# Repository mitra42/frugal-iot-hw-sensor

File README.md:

# Frugal-IoT V0.2

A simple, un-opinionated, multi-purpose sensor board, that can be wired to sensors using most common interfaces (I2C, ModBus, OneWire, Analog) with onboard charging and external antenna.

**Status:** revision 4 (28 Oct 2026): 64 × 37 mm, 2 layers, routed, DRC clean; J4 (cell) and J6 (5 V in) now fitted (D34); JLCPCB files ready for the first order.

## Hardware Features

* ESP32-C3-WROOM-02U
* U.FL socket for external antenna. 
* USB-C for power and programming (e.g. using a $10 security camera solar panel)
* Protected charger circuitry for a single LiPo cell (~250mA), will work with really small cells (e.g. salvaged from vapes) or by adding a solder bridge can charge an 18650 cell at ~500mA
* Sensors controlled by a switched 3.3V sensor rail, allowing much lower power consumption in sleep.
* I2C support on J1 
* Two sensor inputs on J12 can be used for analog, OneWire etc, pads to add pull up resistor or smoothing capacitor if required.
* Two extra sensors on J13 (not soldered by default) 
* RS485(Modbus) on J3, (can be omitted to save ~USD1.00, or to get three more pins for sensors.
* 37mm * 64mm board with connectors mostly at the ends, so that it can fit inside a 40mm pipe as an affordable enclosure. 

## Software features

The board can be flashed with any software, but its designed to work well with [Frugal-IoT](https://github.com/mitra42/frugal-iot) which has the following features. 

* Support for a very wide and expanding range of sensors 
* Integrates with Frugal-IoT cloud, and UX on phone or laptop
* Plug and play MQTT interface, treats remote sensors and actuators the same as local ones 
* Captive WiFi portal for local configuration
* Local controls for on-device automation configured through the UX.
* Multilingual support on both captive portal and UX
* Automatic Over-The-Air (OTA) updates for unattended devices.
* Power management for really long life for sensors that report at long intervals.
* mDNS, for device to device signalling when the Internet is down
* NTP integration for accurate clock
* Fully Open-Source (i.e. not crippleware) 

## Files

| | |
|---|---|
| `SCHEMATIC.pdf` | schematic, one sheet |
| `BOM.csv` | bill of materials with LCSC (JLCPCB) part numbers; DNP = not fitted |
| `COST-ESTIMATE.txt` | JLCPCB cost for 10 and 100 boards, and the saving without Modbus |
| `PCB-LAYOUT.pdf` | 3D views and both copper layers |
| `DECISIONS.md` | design decisions and why |
| `fabrication/` | files to order from JLCPCB — see its README |
| `frugal_iot_v02/` | KiCad 10 project |
| `firmware/` | PlatformIO env for frugal-iot-demo + board variant (pins_arduino.h) |
| `claude-tools/` | scripts Claude uses to regenerate the design — reviewers can ignore |

The schematic is generated from `claude-tools/schematic/circuit.py`: changes made by Claude go there, not into
the .kicad_sch. Regenerate: `buildlib.py`, `run_draw_bg.sh` (log must end `VERIFY OK`), `run_kicad.sh`,
then `jlc_dump.sh` and `python3 cost_estimate.py > ../../COST-ESTIMATE.txt` (see ../irrigation-layout-oct-2026/claude-tools/README.md for the method).

If the fabrication and KiCad directories are not available wherever you find this, please let me know (mitra@mitra.biz) and I'll send you them.

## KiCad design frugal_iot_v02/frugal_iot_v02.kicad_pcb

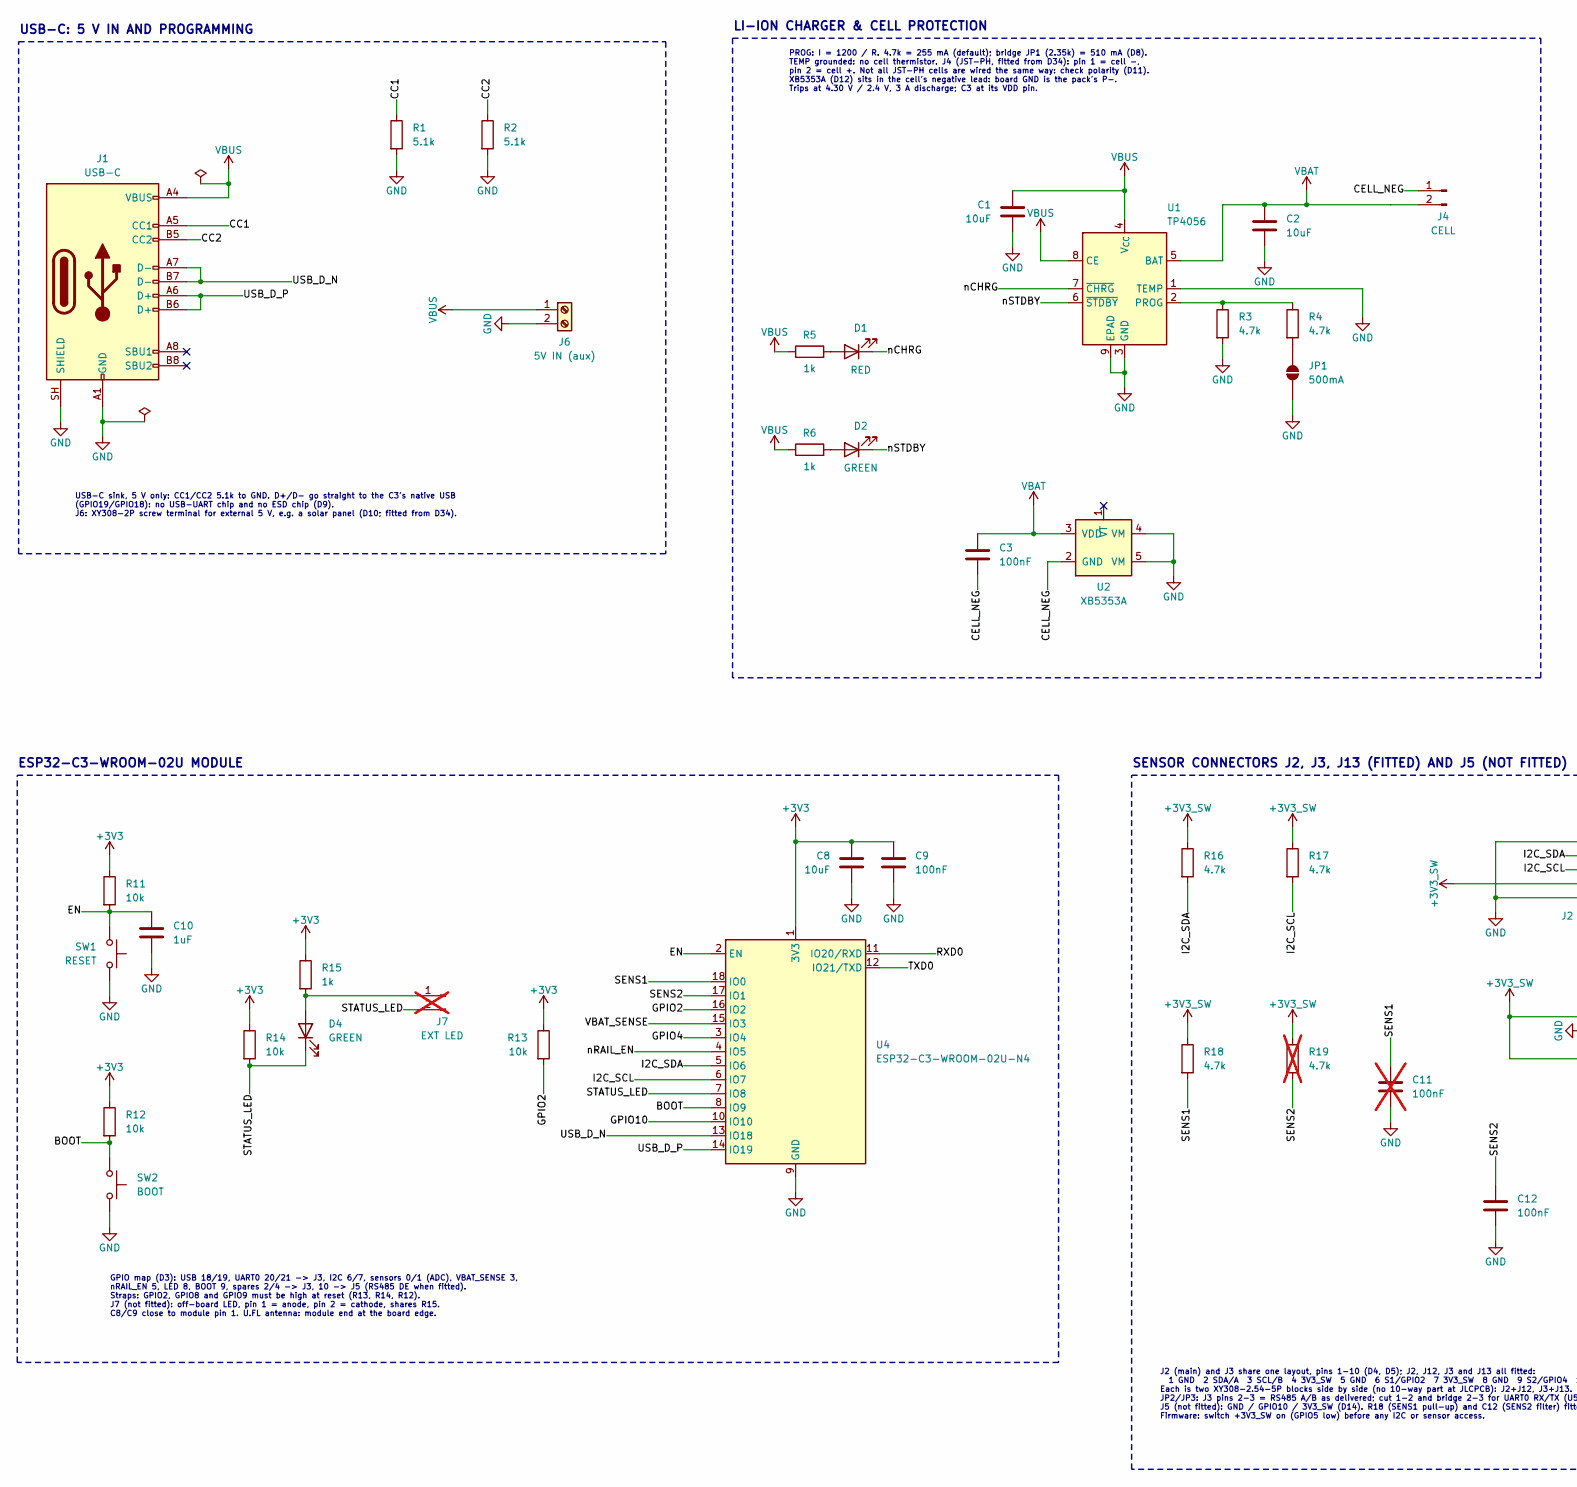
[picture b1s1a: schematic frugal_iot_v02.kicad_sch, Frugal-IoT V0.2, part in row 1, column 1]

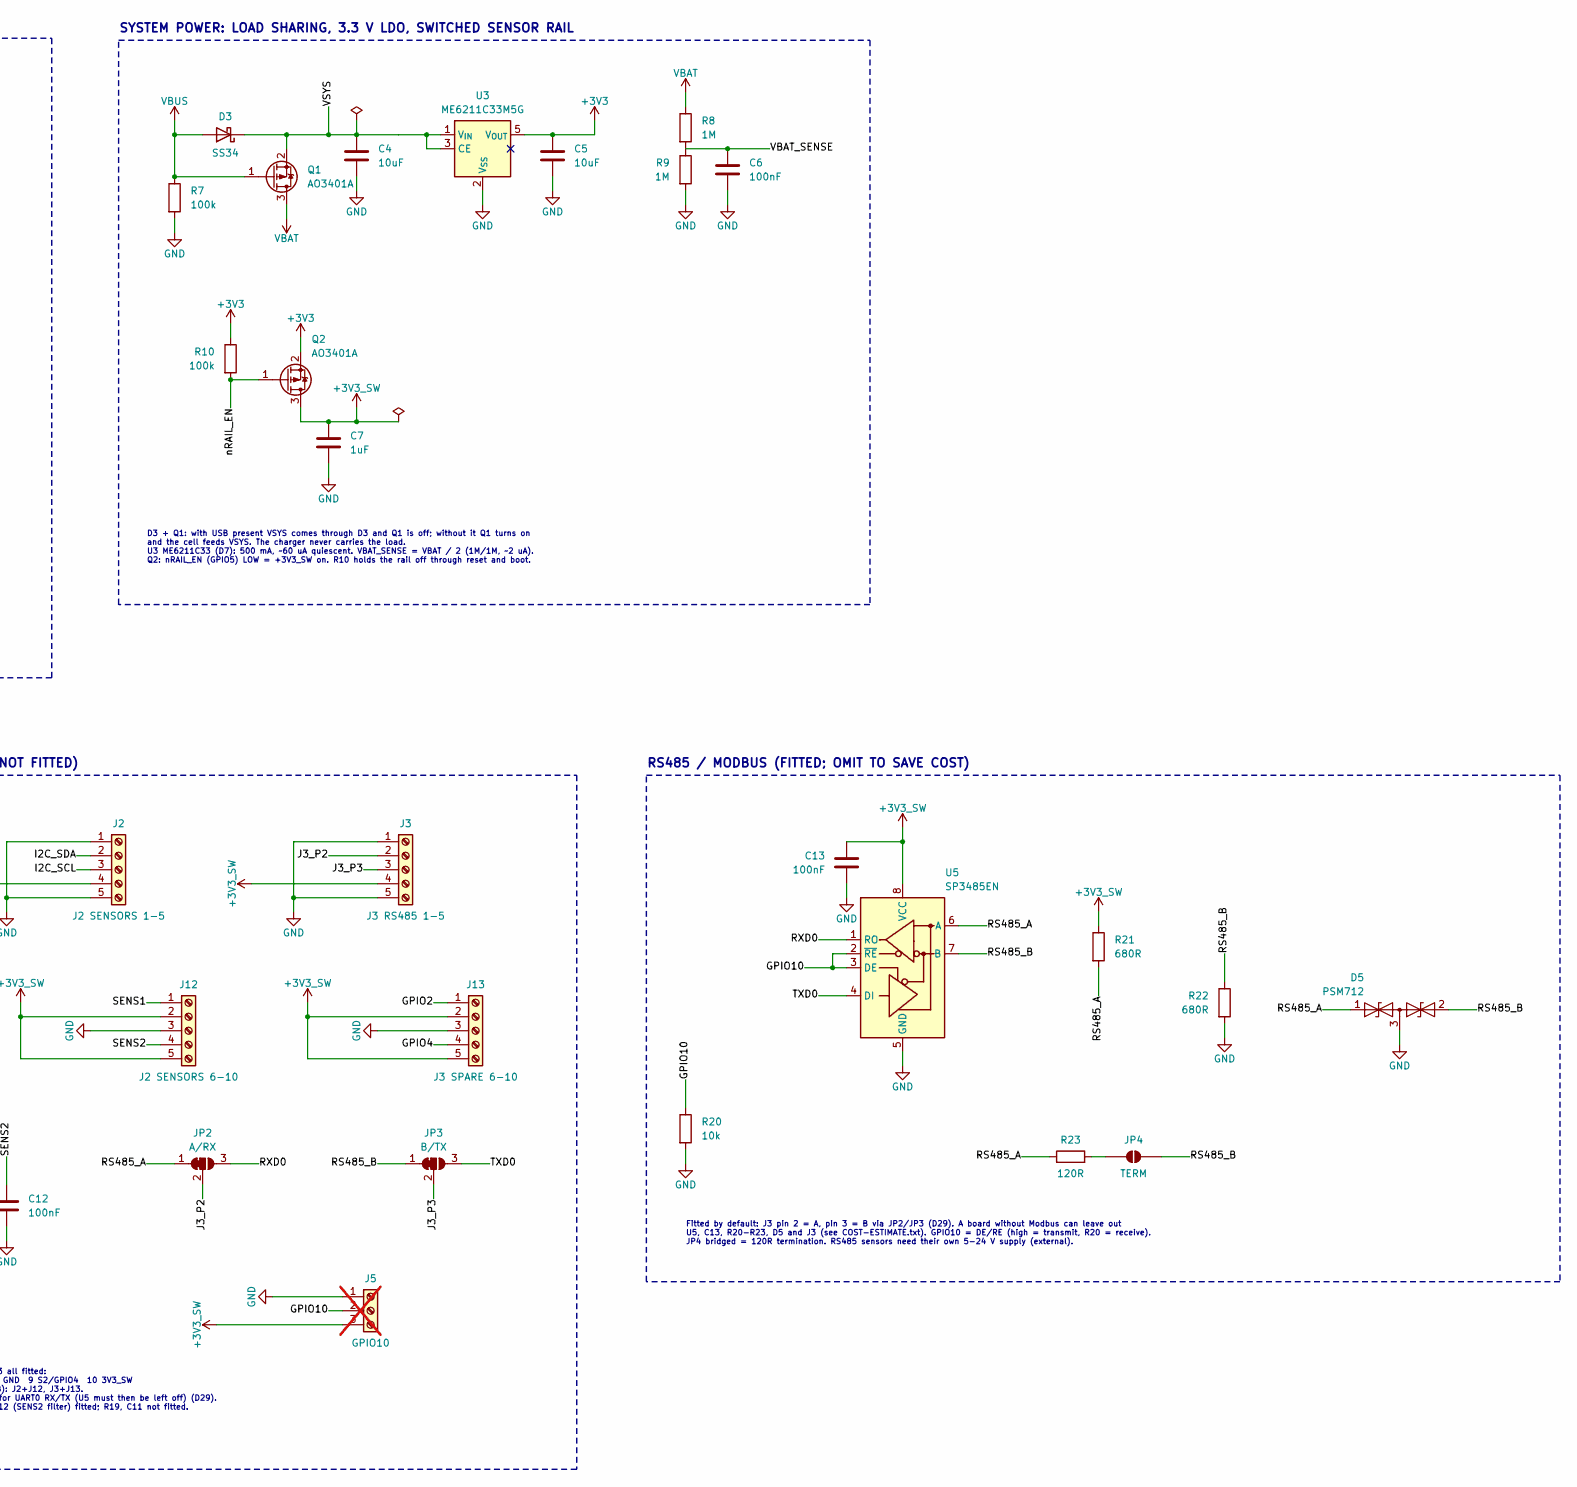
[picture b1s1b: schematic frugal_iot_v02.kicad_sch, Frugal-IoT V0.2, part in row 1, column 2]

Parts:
C1, C2, C4, C5, C8: 10uF; C_0603_1608Metric; MPN 10uF; LCSC C19702
C3, C6, C9, C12, C13: 100nF; C_0603_1608Metric; MPN 100nF; LCSC C14663
C7, C10: 1uF; C_0603_1608Metric; MPN 1uF; LCSC C15849
C11: 100nF; C_0603_1608Metric; MPN 100nF; LCSC C14663; not fitted
D1: RED; LED_0603_1608Metric; MPN KT-0603R; LCSC C2286
D2, D4: GREEN; LED_0805_2012Metric; MPN KT-0805G; LCSC C2297
D3: SS34; D_SMA; MPN SS34; LCSC C8678
D5: PSM712; SOT-23; MPN PSM712-LF-T7; LCSC C32677
J1: USB-C; USB_C_Receptacle_HRO_TYPE-C-31-M-12; MPN TYPE-C-31-M-12; LCSC C165948
J2: J2 SENSORS 1-5; TerminalBlock_Xinya_XY308-2.54-5P_1x05_P2.54mm_Horizontal; MPN XY308-2.54-5P; LCSC C915914
J3: J3 RS485 1-5; TerminalBlock_Xinya_XY308-2.54-5P_1x05_P2.54mm_Horizontal; MPN XY308-2.54-5P; LCSC C915914
J4: CELL; JST_PH_S2B-PH-K_1x02_P2.00mm_Horizontal; MPN S2B-PH-K-S; LCSC C173752
J5: GPIO10; TerminalBlock_Xinya_XY308-2.54-3P_1x03_P2.54mm_Horizontal; MPN XY308-2.54-3P; LCSC C557686; not fitted
J6: 5V IN (aux); TerminalBlock_Xinya_XY308-2.54-2P_1x02_P2.54mm_Horizontal; MPN XY308-2.54-2P; LCSC C557685
J7: EXT LED; PinHeader_1x02_P2.54mm_Vertical; MPN EXT LED; not fitted
J12: J2 SENSORS 6-10; TerminalBlock_Xinya_XY308-2.54-5P_1x05_P2.54mm_Horizontal; MPN XY308-2.54-5P; LCSC C915914
J13: J3 SPARE 6-10; TerminalBlock_Xinya_XY308-2.54-5P_1x05_P2.54mm_Horizontal; MPN XY308-2.54-5P; LCSC C915914
JP1: 500mA; SolderJumper-2_P1.3mm_Open_RoundedPad1.0x1.5mm; MPN 500mA
JP2: A/RX; SolderJumper-3_P1.3mm_Bridged12_RoundedPad1.0x1.5mm; MPN A/RX
JP3: B/TX; SolderJumper-3_P1.3mm_Bridged12_RoundedPad1.0x1.5mm; MPN B/TX
JP4: TERM; SolderJumper-2_P1.3mm_Open_RoundedPad1.0x1.5mm; MPN TERM
Q1, Q2: AO3401A; SOT-23; MPN AO3401A; LCSC C15127
R1, R2: 5.1k; R_0603_1608Metric; MPN 5.1k; LCSC C23186
R3, R4, R16, R17, R18: 4.7k; R_0603_1608Metric; MPN 4.7k; LCSC C23162
R5, R6, R15: 1k; R_0603_1608Metric; MPN 1k; LCSC C21190
R7, R10: 100k; R_0603_1608Metric; MPN 100k; LCSC C25803
R8, R9: 1M; R_0603_1608Metric; MPN 1M; LCSC C22935
R11, R12, R13, R14, R20: 10k; R_0603_1608Metric; MPN 10k; LCSC C25804
R19: 4.7k; R_0603_1608Metric; MPN 4.7k; LCSC C23162; not fitted
R21, R22: 680R; R_0603_1608Metric; MPN 680R; LCSC C23228
R23: 120R; R_0603_1608Metric; MPN 120R; LCSC C22787
SW1: RESET; SW_Push_1P1T_XKB_TS-1187A; MPN TS-1187A-B-A-B; LCSC C318884
SW2: BOOT; SW_Push_1P1T_XKB_TS-1187A; MPN TS-1187A-B-A-B; LCSC C318884
U1: TP4056; SOIC-8-1EP_3.9x4.9mm_P1.27mm_EP2.41x3.3mm; MPN TP4056; LCSC C16581
U2: XB5353A; SOT-23-5; MPN XB5353A; LCSC C80628
U3: ME6211C33M5G; SOT-23-5; MPN ME6211C33M5G-N; LCSC C82942
U4: ESP32-C3-WROOM-02U-N4; ESP32-C3-WROOM-02U; MPN ESP32-C3-WROOM-02U-N4; LCSC C2926676
U5: SP3485EN; SOIC-8_3.9x4.9mm_P1.27mm; MPN SP3485EN-L/TR; LCSC C8963

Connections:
+3V3: C5.1, C8.1, C9.1, Q2.2 (S), R10.1, R11.1, R12.1, R13.1, R14.1, R15.1, U3.5 (V_{OUT}), U4.1 (3V3)
/BOOT: R12.2, SW2.1, U4.8 (IO9)
/CC1: J1.A5 (CC1), R1.1
/CC2: J1.B5 (CC2), R2.1
/CELL_NEG: C3.2, J4.1, U2.2 (GND)
/EN: C10.1, R11.2, SW1.1, U4.2 (EN)
/GPIO2: J13.1, R13.2, U4.16 (IO2)
/GPIO4: J13.4, U4.3 (IO4)
/GPIO10: J5.2, R20.1, U4.10 (IO10), U5.2 (~RE), U5.3 (DE)
/I2C_SCL: J2.3, R17.2, U4.6 (IO7)
/I2C_SDA: J2.2, R16.2, U4.5 (IO6)
/J3_P2: J3.2, JP2.2 (C)
/J3_P3: J3.3, JP3.2 (C)
/RS485_A: D5.1 (A1), JP2.1 (A), R21.2, R23.1, U5.6 (A)
/RS485_B: D5.2 (A2), JP3.1 (A), JP4.2 (B), R22.1, U5.7 (B)
/RXD0: JP2.3 (B), U4.11 (IO20/RXD), U5.1 (RO)
/SENS1: C11.1, J12.1, R18.2, U4.18 (IO0)
/SENS2: C12.1, J12.4, R19.2, U4.17 (IO1)
/STATUS_LED: D4.1 (K), J7.2, R14.2, U4.7 (IO8)
/TXD0: JP3.3 (B), U4.12 (IO21/TXD), U5.4 (DI)
/USB_D_N: J1.A7 (D-), J1.B7 (D-), U4.13 (IO18)
/USB_D_P: J1.A6 (D+), J1.B6 (D+), U4.14 (IO19)
/VBAT_SENSE: C6.1, R8.2, R9.1, U4.15 (IO3)
/nCHRG: D1.1 (K), U1.7 (~CHRG)
/nRAIL_EN: Q2.1 (G), R10.2, U4.4 (IO5)
/nSTDBY: D2.1 (K), U1.6 (~STDBY)
unnamed: D1.2 (A), R5.2
unnamed: D2.2 (A), R6.2
unnamed: D4.2 (A), J7.1, R15.2
unnamed: JP1.1 (A), R4.2
unnamed: JP4.1 (A), R23.2
unnamed: R3.1, R4.1, U1.2 (PROG)
VBAT: C2.1, C3.1, J4.2, Q1.3 (D), R8.1, U1.5 (BAT), U2.3 (VDD)

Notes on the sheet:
D3 + Q1: with USB present VSYS comes through D3 and Q1 is off; without it Q1 turns on and the cell feeds VSYS. The charger never carries the load. U3 ME6211C33 (D7): 500 mA, ~60 uA quiescent. VBAT_SENSE = VBAT / 2 (1M/1M, ~2 uA). Q2: nRAIL_EN (GPIO5) LOW = +3V3_SW on. R10 holds the rail off through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
ESP32-C3-WROOM-02U MODULE
RS485 / MODBUS (FITTED; OMIT TO SAVE COST)
J2 (main) and J3 share one layout, pins 1-10 (D4, D5); J2, J12, J3 and J13 all fitted: 1 GND 2 SDA/A 3 SCL/B 4 3V3_SW 5 GND 6 S1/GPIO2 7 3V3_SW 8 GND 9 S2/GPIO4 10 3V3_SW Each is two XY308-2.54-5P blocks side by side (no 10-way part at JLCPCB): J2+J12, J3+J13. JP2/JP3: J3 pins 2-3 = RS485 A/B as de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
GPIO map (D3): USB 18/19, UART0 20/21 -> J3, I2C 6/7, sensors 0/1 (ADC), VBAT_SENSE 3, nRAIL_EN 5, LED 8, BOOT 9, spares 2/4 -> J3, 10 -> J5 (RS485 DE when fitted). Straps: GPIO2, GPIO8 and GPIO9 must be high at reset (R13, R14, R12). J7 (not fitted): off-board LED, pin 1 = anode, pin 2 = cathode, 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
LI-ION CHARGER & CELL PROTECTION
USB-C sink, 5 V only: CC1/CC2 5.1k to GND. D+/D- go straight to the C3's native USB (GPIO19/GPIO18): no USB-UART chip and no ESD chip (D9). J6: XY308-2P screw terminal for external 5 V, e.g. a solar panel (D10; fitted from D34).
SYSTEM POWER: LOAD SHARING, 3.3 V LDO, SWITCHED SENSOR RAIL
PROG: I = 1200 / R. 4.7k = 255 mA (default); bridge JP1 (2.35k) = 510 mA (D8). TEMP grounded: no cell thermistor. J4 (JST-PH, fitted from D34): pin 1 = cell -, pin 2 = cell +. Not all JST-PH cells are wired the same way: check polarity (D11). XB5353A (D12) sits in the cell's negative lead: board GN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
USB-C: 5 V IN AND PROGRAMMING
Fitted by default: J3 pin 2 = A, pin 3 = B via JP2/JP3 (D29). A board without Modbus can leave out U5, C13, R20-R23, D5 and J3 (see COST-ESTIMATE.txt). GPIO10 = DE/RE (high = transmit, R20 = receive). JP4 bridged = 120R termination. RS485 sensors need their own 5-24 V supply (external).
SENSOR CONNECTORS J2, J3, J13 (FITTED) AND J5 (NOT FITTED)

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
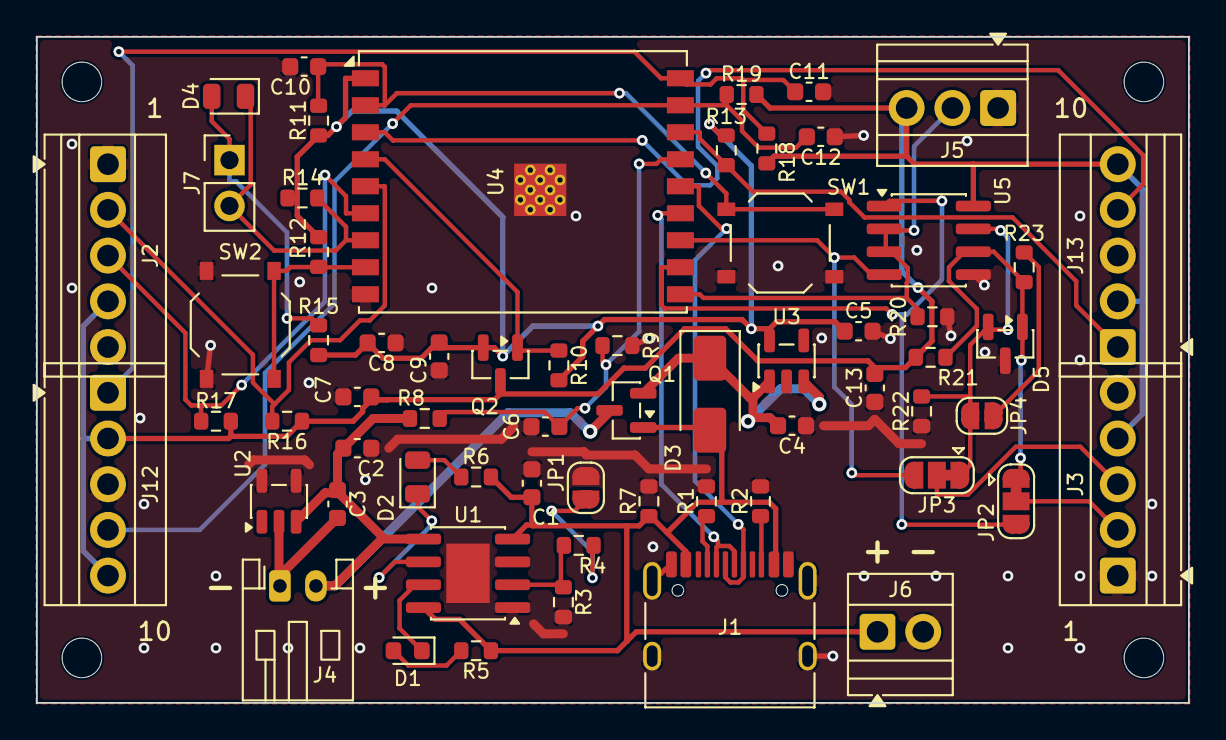
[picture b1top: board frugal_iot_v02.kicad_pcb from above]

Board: 2 copper layers, 64.0 x 37.0 mm, 67 parts (0 on the bottom side), 37 nets.

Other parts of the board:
H1, H2, H3, H4: M2; MountingHole_2.2mm_M2

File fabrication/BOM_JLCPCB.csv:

Comment,Designator,Footprint,LCSC Part #
10uF,"C1,C2,C4,C5,C8",C_0603_1608Metric,C19702
100nF,"C3,C6,C9,C12,C13",C_0603_1608Metric,C14663
1uF,"C7,C10",C_0603_1608Metric,C15849
RED,D1,LED_0603_1608Metric,C2286
GREEN,"D2,D4",LED_0805_2012Metric,C2297
SS34,D3,D_SMA,C8678
PSM712,D5,SOT-23,C32677
USB-C,J1,USB_C_Receptacle_HRO_TYPE-C-31-M-12,C165948
J2 SENSORS 1-5,"J2,J3,J12,J13",TerminalBlock_Xinya_XY308-2.54-5P_1x05_P2.54mm_Horizontal,C915914
CELL,J4,JST_PH_S2B-PH-K_1x02_P2.00mm_Horizontal,C173752
5V IN (aux),J6,TerminalBlock_Xinya_XY308-2.54-2P_1x02_P2.54mm_Horizontal,C557685
AO3401A,"Q1,Q2",SOT-23,C15127
5.1k,"R1,R2",R_0603_1608Metric,C23186
4.7k,"R3,R4,R16,R17,R18",R_0603_1608Metric,C23162
1k,"R5,R6,R15",R_0603_1608Metric,C21190
100k,"R7,R10",R_0603_1608Metric,C25803
1M,"R8,R9",R_0603_1608Metric,C22935
10k,"R11,R12,R13,R14,R20",R_0603_1608Metric,C25804
680R,"R21,R22",R_0603_1608Metric,C23228
120R,R23,R_0603_1608Metric,C22787
RESET,"SW1,SW2",SW_Push_1P1T_XKB_TS-1187A,C318884
TP4056,U1,SOIC-8-1EP_3.9x4.9mm_P1.27mm_EP2.41x3.3mm,C16581
XB5353A,U2,SOT-23-5,C80628
ME6211C33M5G,U3,SOT-23-5,C82942
ESP32-C3-WROOM-02U-N4,U4,ESP32-C3-WROOM-02U,C2926676
SP3485EN,U5,SOIC-8_3.9x4.9mm_P1.27mm,C8963

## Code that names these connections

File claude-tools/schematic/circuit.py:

"""Circuit definition for Frugal-IoT V0.2 (source of truth for parts and nets).
Each part: dict(prefix, lib, value, fp, nets{pin:net}, dnp, lcsc, mpn, block, note, ref)
net 'NC' => no-connect marker. Decisions referenced as Dn are in ../../DECISIONS.md.
"""
P = []
def part(prefix, lib, value, fp, nets, block, dnp=False, lcsc='', mpn='', rot=None, note='', ref=None):
    P.append(dict(prefix=prefix, lib=lib, value=value, fp=fp, nets=nets, block=block,
                  dnp=dnp, lcsc=lcsc, mpn=mpn, rot=rot, note=note, ref=ref))

R06 = 'Resistor_SMD:R_0603_1608Metric'; C06 = 'Capacitor_SMD:C_0603_1608Metric'
LED06 = 'LED_SMD:LED_0603_1608Metric'; LED08 = 'LED_SMD:LED_0805_2012Metric'
SMA = 'Diode_SMD:D_SMA'; SOT23 = 'Package_TO_SOT_SMD:SOT-23'
TB254 = 'TerminalBlock:TerminalBlock_Xinya_XY308-2.54-{n}P_1x0{n}_P2.54mm_Horizontal'
HDR = 'Connector_PinHeader_2.54mm:PinHeader_1x0{n}_P2.54mm_Vertical'
BTN = 'Button_Switch_SMD:SW_Push_1P1T_XKB_TS-1187A'
SJ = 'Jumper:SolderJumper-2_P1.3mm_Open_RoundedPad1.0x1.5mm'
SJ3 = 'Jumper:SolderJumper-3_P1.3mm_Bridged12_RoundedPad1.0x1.5mm'
XY = {2: ('C557685', 'XY308-2.54-2P'), 3: ('C557686', 'XY308-2.54-3P'), 5: ('C915914', 'XY308-2.54-5P')}

RES = {'10k': 'C25804', '100k': 'C25803', '1k': 'C21190', '4.7k': 'C23162', '5.1k': 'C23186',
       '1M': 'C22935', '120R': 'C22787', '680R': 'C23228'}
CAP = {'100nF': 'C14663', '1uF': 'C15849', '10uF': 'C19702'}

def R(v, a, b, blk, dnp=False, note=''):
    part('R', 'Device:R', v, R06, {'1': a, '2': b}, blk, dnp, RES.get(v, ''), note=note)
def C(v, a, b, blk, dnp=False, note=''):
    part('C', 'Device:C', v, C06, {'1': a, '2': b}, blk, dnp, CAP.get(v, ''), note=note)
def LED(col, anode, cathode, blk):  # JLCPCB Basic: red KT-0603R, green KT-0805G
    part('D', 'Device:LED', col, {'RED': LED06, 'GREEN': LED08}[col], {'2': anode, '1': cathode}, blk, rot=180,
         lcsc={'RED': 'C2286', 'GREEN': 'C2297'}[col], mpn={'RED': 'KT-0603R', 'GREEN': 'KT-0805G'}[col])
def PFET(g, s, d, blk):
    part('Q', 'Transistor_FET:AO3401A', 'AO3401A', SOT23, {'1': g, '2': s, '3': d}, blk, lcsc='C15127')
def BUTTON(a, b, blk, val):
    part('SW', 'Switch:SW_Push', val, BTN, {'1': a, '2': b}, blk, lcsc='C318884', mpn='TS-1187A-B-A-B')
def TERM(ref, n, nets, blk, val, dnp=False):
    lc, mpn = XY[n]
    part('J', f'Connector:Screw_Terminal_01x0{n}', val, TB254.format(n=n),
         {str(i + 1): net for i, net in enumerate(nets)}, blk, dnp, lc, mpn, ref=ref)

# ---------------- USB-C (power + native USB) ----------------
B = 'usb'
part('J', 'Connector:USB_C_Receptacle_USB2.0_16P', 'USB-C', 'Connector_USB:USB_C_Receptacle_HRO_TYPE-C-31-M-12',
     {'A1': 'GND', 'B1': 'GND', 'A12': 'GND', 'B12': 'GND', 'A4': 'VBUS', 'A9': 'VBUS', 'B4': 'VBUS', 'B9': 'VBUS',
      'A5': 'CC1', 'B5': 'CC2', 'A6': 'USB_D_P', 'B6': 'USB_D_P', 'A7': 'USB_D_N', 'B7': 'USB_D_N',
      'A8': 'NC', 'B8': 'NC', 'SH': 'GND'}, B, lcsc='C165948', mpn='TYPE-C-31-M-12', ref='J1')
R('5.1k', 'CC1', 'GND', B); R('5.1k', 'CC2', 'GND', B)
TERM('J6', 2, ['VBUS', 'GND'], B, '5V IN (aux)')   # D10: external 5 V beside USB; fitted from D34

# ---------------- Charger + cell protection ----------------
B = 'chg'
part('U', 'Battery_Management:TP4056-42-ESOP8', 'TP4056', 'Package_SO:SOIC-8-1EP_3.9x4.9mm_P1.27mm_EP2.41x3.3mm',
     {'1': 'GND', '2': 'CHG_PROG', '3': 'GND', '4': 'VBUS', '5': 'VBAT', '6': 'nSTDBY', '7': 'nCHRG',
      '8': 'VBUS', '9': 'GND'}, B, lcsc='C16581', note='TEMP grounded: no cell NTC')
C('10uF', 'VBUS', 'GND', B); C('10uF', 'VBAT', 'GND', B)
R('4.7k', 'CHG_PROG', 'GND', B, note='~250 mA')
R('4.7k', 'CHG_PROG', 'CHG_PROG2', B, note='with JP1: ~500 mA')
part('JP', 'Jumper:SolderJumper_2_Open', '500mA', SJ, {'1': 'CHG_PROG2', '2': 'GND'}, B)
R('1k', 'VBUS', 'LED_CHRG', B); LED('RED', 'LED_CHRG', 'nCHRG', B)
R('1k', 'VBUS', 'LED_STDBY', B); LED('GREEN', 'LED_STDBY', 'nSTDBY', B)
part('J', 'Connector:Conn_01x02_Pin', 'CELL', 'Connector_JST:JST_PH_S2B-PH-K_1x02_P2.00mm_Horizontal',
     {'1': 'CELL_NEG', '2': 'VBAT'}, B, lcsc='C173752', mpn='S2B-PH-K-S', ref='J4')
part('U', 'frugal:XB5353A', 'XB5353A', 'Package_TO_SOT_SMD:SOT-23-5',
     {'1': 'NC', '2': 'CELL_NEG', '3': 'VBAT', '4': 'GND', '5': 'GND'}, B, lcsc='C80628', mpn='XB5353A')
C('100nF', 'VBAT', 'CELL_NEG', B)

# ---------------- System power ----------------
B = 'pwr'
part('D', 'Device:D_Schottky', 'SS34', SMA, {'2': 'VBUS', '1': 'VSYS'}, B, lcsc='C8678', mpn='SS34', rot=180)
PFET('VBUS', 'VSYS', 'VBAT', B)                  # load sharing: cell feeds VSYS when USB is absent
R('100k', 'VBUS', 'GND', B)
C('10uF', 'VSYS', 'GND', B)
part('U', 'Regulator_Linear:ME6211C33M5', 'ME6211C33M5G', 'Package_TO_SOT_SMD:SOT-23-5',
     {'1': 'VSYS', '3': 'VSYS', '2': 'GND', '4': 'NC', '5': '+3V3'}, B, lcsc='C82942', mpn='ME6211C33M5G-N')
C('10uF', '+3V3', 'GND', B)
R('1M', 'VBAT', 'VBAT_SENSE', B); R('1M', 'VBAT_SENSE', 'GND', B); C('100nF', 'VBAT_SENSE', 'GND', B)
PFET('nRAIL_EN', '+3V3', '+3V3_SW', B)           # GPIO5 low = sensors on; pull-up keeps it off at reset
R('100k', '+3V3', 'nRAIL_EN', B, note='rail off at reset')
C('1uF', '+3V3_SW', 'GND', B)

# ---------------- MCU ----------------
B = 'mcu'
part('U', 'RF_Module:ESP32-C3-WROOM-02U', 'ESP32-C3-WROOM-02U-N4', 'RF_Module:ESP32-C3-WROOM-02U',
     {'1': '+3V3', '2': 'EN', '3': 'GPIO4', '4': 'nRAIL_EN', '5': 'I2C_SDA', '6': 'I2C_SCL', '7': 'STATUS_LED',
      '8': 'BOOT', '9': 'GND', '10': 'GPIO10', '11': 'RXD0', '12': 'TXD0', '13': 'USB_D_N', '14': 'USB_D_P',
      '15': 'VBAT_SENSE', '16': 'GPIO2', '17': 'SENS2', '18': 'SENS1', '19': 'GND'},
     B, lcsc='C2926676', mpn='ESP32-C3-WROOM-02U-N4')
C('10uF', '+3V3', 'GND', B); C('100nF', '+3V3', 'GND', B)
R('10k', '+3V3', 'EN', B); C('1uF', 'EN', 'GND', B); BUTTON('EN', 'GND', B, 'RESET')
R('10k', '+3V3', 'BOOT', B); BUTTON('BOOT', 'GND', B, 'BOOT')
R('10k', '+3V3', 'GPIO2', B, note='GPIO2 strap high')
R('10k', '+3V3', 'STATUS_LED', B, note='GPIO8 strap high')
R('1k', '+3V3', 'LED_STAT', B); LED('GREEN', 'LED_STAT', 'STATUS_LED', B)
part('J', 'Connector:Conn_01x02_Pin', 'EXT LED', HDR.format(n=2), {'1': 'LED_STAT', '2': 'STATUS_LED'}, B,
     dnp=True, ref='J7', note='off-board LED: 1 = anode, 2 = cathode')

# ---------------- Sensor connectors ----------------
B = 'conn'
R('4.7k', '+3V3_SW', 'I2C_SDA', B); R('4.7k', '+3V3_SW', 'I2C_SCL', B)
# Fitted (D31): R18 = SENS1 pull-up (e.g. DS18B20), C12 = SENS2 filter (analog). R19, C11 stay options.
for s, fit_r, fit_c in (('SENS1', True, False), ('SENS2', False, True)):
    R('4.7k', '+3V3_SW', s, B, dnp=not fit_r, note='pull-up (e.g. DS18B20)' if fit_r else 'pull-up option (e.g. DS18B20)')
    C('100nF', s, 'GND', B, dnp=not fit_c, note='filter (analog)' if fit_c else 'filter option (analog)')
# J2: main sensor connector (fitted) = two 5-way XY308 side by side, pins 1-10 as v0.1 (D4)
TERM('J2', 5, ['GND', 'I2C_SDA', 'I2C_SCL', '+3V3_SW', 'GND'], B, 'J2 SENSORS 1-5')
TERM('J12', 5, ['SENS1', '+3V3_SW', 'GND', 'SENS2', '+3V3_SW'], B, 'J2 SENSORS 6-10')
# J3: same layout (D5); pins 2-3 = RS485 A/B as delivered (JP2/JP3 bridged 1-2), or UART RX/TX (cut, bridge 2-3)
TERM('J3', 5, ['GND', 'J3_P2', 'J3_P3', '+3V3_SW', 'GND'], B, 'J3 RS485 1-5')   # fitted with the RS485 option (D29)
TERM('J13', 5, ['GPIO2', '+3V3_SW', 'GND', 'GPIO4', '+3V3_SW'], B, 'J3 SPARE 6-10')   # fitted (D31)
part('JP', 'Jumper:SolderJumper_3_Bridged12', 'A/RX', SJ3, {'1': 'RS485_A', '2': 'J3_P2', '3': 'RXD0'}, B)
part('JP', 'Jumper:SolderJumper_3_Bridged12', 'B/TX', SJ3, {'1': 'RS485_B', '2': 'J3_P3', '3': 'TXD0'}, B)
TERM('J5', 3, ['GND', 'GPIO10', '+3V3_SW'], B, 'GPIO10', dnp=True)   # D14

# ---------------- RS485 option (fitted by default, D29; omit to save cost) ----------------
B = 'rs485'
part('U', 'Interface_UART:SP3485EN', 'SP3485EN', 'Package_SO:SOIC-8_3.9x4.9mm_P1.27mm',
     {'1': 'RXD0', '2': 'GPIO10', '3': 'GPIO10', '4': 'TXD0', '5': 'GND', '6': 'RS485_A', '7': 'RS485_B',
      '8': '+3V3_SW'}, B, lcsc='C8963', mpn='SP3485EN-L/TR')
C('100nF', '+3V3_SW', 'GND', B)
R('10k', 'GPIO10', 'GND', B, note='receive by default')
R('680R', '+3V3_SW', 'RS485_A', B, note='bias'); R('680R', 'RS485_B', 'GND', B, note='bias')
R('120R', 'RS485_A', 'RS485_TERM', B)
part('JP', 'Jumper:SolderJumper_2_Open', 'TERM', SJ, {'1': 'RS485_TERM', '2': 'RS485_B'}, B)
part('D', 'Diode:SM712_SOT23', 'PSM712', SOT23, {'1': 'RS485_A', '2': 'RS485_B', '3': 'GND'}, B,
     lcsc='C32677', mpn='PSM712-LF-T7')
